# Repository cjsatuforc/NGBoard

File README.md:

# NGBoard
Next generation 3d printer controller board
## TODO
* Development
  * PCB Layout
  * BOM/Parts list
  * Switching regulator test
* Production
  * Software
  * Testing
* Profit

## Features
* 32 bit microcontroller (STM32F401VET)
* Trinamic tmc2130 drivers
* Raspberry pi/orange pi connector
* 12V or 24V 
* Direct connect inductive sensor

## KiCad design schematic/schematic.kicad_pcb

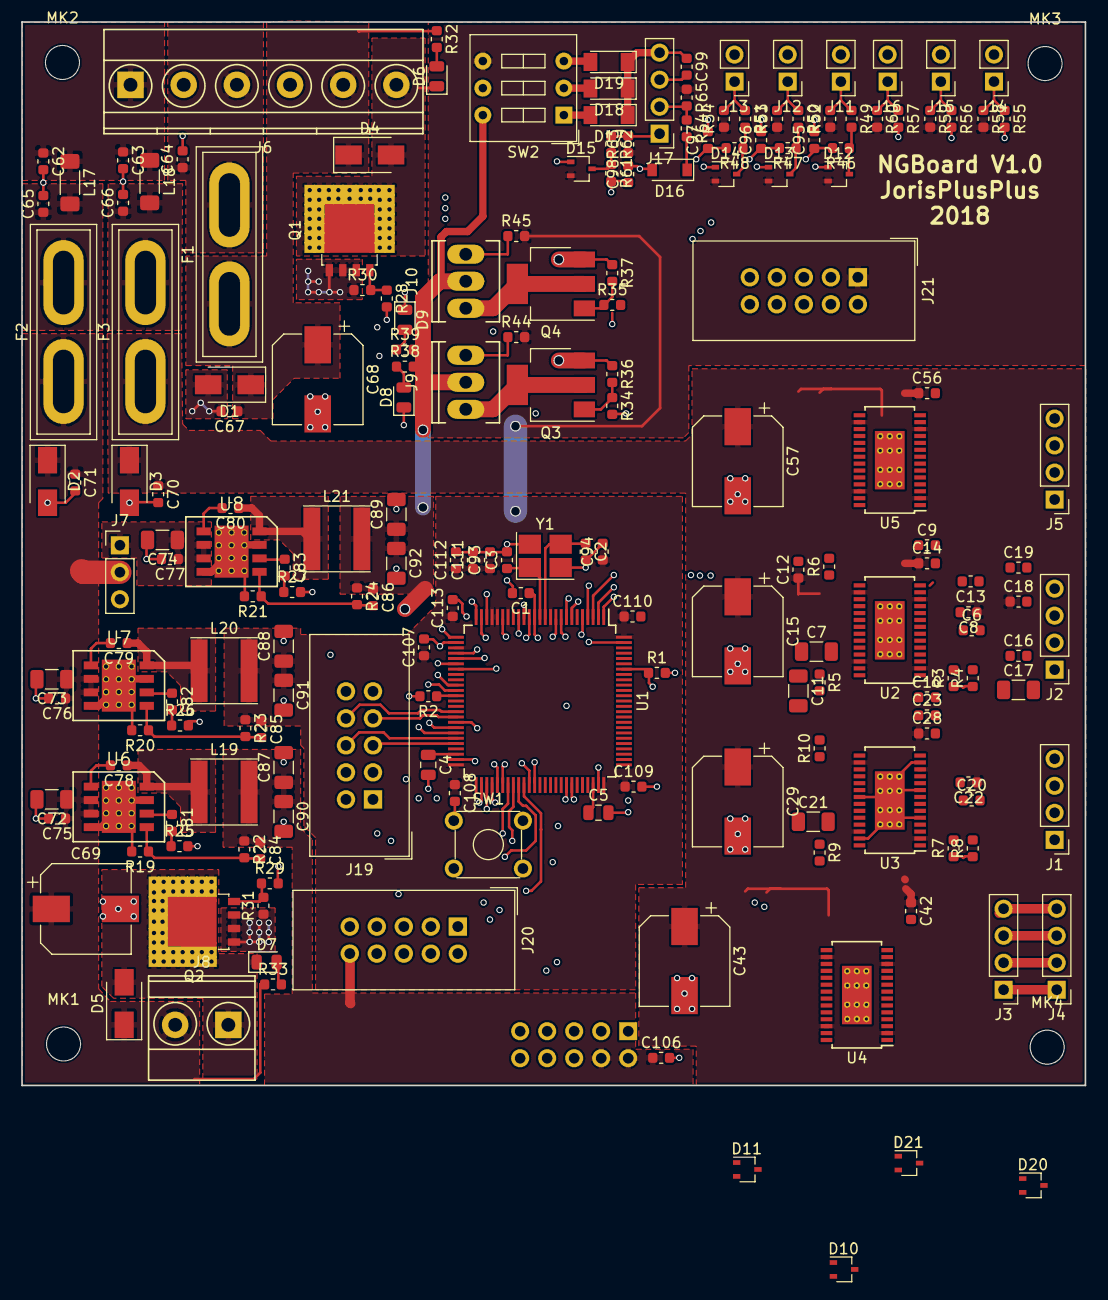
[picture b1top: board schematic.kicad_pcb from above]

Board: 4 copper layers, 100.0 x 100.0 mm, 197 parts (1 on the bottom side), 140 nets.

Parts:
C1, C6, C10, C16, C20, C62, C63, C64, C65, C66, C67, C70, C71, C75, C76, C77, C78, C79, C80, C94, C95, C96, C97, C98, C99, C106, C107, C108, C109, C110, C111, C112: 100nF; C_0603_1608Metric
C2, C3, C84: 18pF; C_0603_1608Metric
C4, C5: 2.2uF; C_0805_2012Metric
C7, C11, C17, C21, C87, C88, C89, C90, C91, C92: 22uF; C_1206_3216Metric
C8, C12, C14, C18, C22, C28, C42, C56: 220nF; C_0603_1608Metric
C9, C13, C19, C23: 10nF; C_0603_1608Metric
C15, C29, C43, C57, C68, C69: 100uF; CP_Elec_8x10
C72, C73, C74: 10uF; C_1206_3216Metric
C81, C82, C83: 6800pF; C_0603_1608Metric
C85, C86: 100pF; C_0603_1608Metric
C93: 4.7uF; C_0603_1608Metric
C113: 1uF; C_0603_1608Metric
D1, D2, D3: SMAJ24A; D_SMA
D4, D5: SK310A; D_SMA
D6, D7, D8, D9: LED; LED_0805_2012Metric
D10, D11, D12, D13, D14, D15, D20, D21: BAV99,215; SOT-323_SC-70
D16: 3.3V; D_SOD-123
D17, D18, D19: D; D_MiniMELF
F1: 15A; BladeFuse-CarType
F2, F3: 5A; BladeFuse-CarType
J1, J2, J3, J4, J5, J17: Conn_01x04; PinHeader_1x04_P2.54mm_Vertical
J6: Conn_01x06; TerminalBlock_Phoenix_MKDS1.5-6pol
J7: Conn_01x03; Socket_Strip_Straight_1x03_Pitch2.54mm
J8: Screw_Terminal_01x02; TerminalBlock_Phoenix_MKDS1.5-2pol
J9, J10: Conn_01x03; Socket_MOLEX-KK-RM2-54mm_Lock_3pin_straight
J11, J12, J13, J14, J15, J16: Conn_01x02; PinHeader_1x02_P2.54mm_Vertical
J18: Conn_02x05_Odd_Even; PinSocket_2x05_P2.54mm_Vertical
J19, J20, J21: Conn_02x05_Odd_Even; IDC-Header_2x05_P2.54mm_Vertical
L17, L18: 60R; L_1806_4516Metric
L19: 4.7uH; L_Taiyo-Yuden_NR-60xx
L20, L21: 3.3uH; L_Taiyo-Yuden_NR-60xx
MK1, MK2, MK3, MK4: Mounting_Hole; MountingHole_3.2mm_M3
Q1, Q2: PSMN1R7-30YL; SOT-669_LFPAK_ThermalVias-1
Q3, Q4: NCV8402; SOT-223
R1, R2, R25, R26, R27, R58, R59, R60, R65: 10K; R_0603_1608Metric
R3, R4, R5, R6, R7, R8, R9, R10: 39K; R_0603_1608Metric
R19: 19.1K; R_0603_1608Metric
R20: 32K; R_0603_1608Metric
R21: 7.15K; R_0603_1608Metric
R22, R23, R24, R30, R31, R36, R37: 100K; R_0603_1608Metric
R28, R29, R34, R35, R55, R56, R57, R64: 100; R_0603_1608Metric
R32, R33, R38, R39, R44, R45: 1.8K; R_0603_1608Metric
R46, R47, R48, R49, R50, R51, R61, R62: 2K37; R_0603_1608Metric
R52, R53, R54, R63: 4.7K; R_0603_1608Metric
SW1: SW_Push_Dual; SW_TH_Tactile_Omron_B3F-10xx
SW2: SW_DIP_x03; SW_DIP_x3_W7.62mm_Slide
U1: STM32F401VETx; LQFP-100_14x14mm_P0.5mm
U2, U3, U4, U5: L6470; HTSSOP-28-L6470
U6, U7, U8: BD9E302EFJ; SOIC-8
Y1: Crystal_GND24; Crystal_SMD_SeikoEpson_FA238-4Pin_3.2x2.5mm_HandSoldering

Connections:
+3V3: C6.1, C7.1, C10.1, C11.1, C16.1, C17.1, C20.1, C21.1, C85.1, C88.1, C91.1, C93.1, C94.1, C107.1, C108.1, C109.1, C110.1, C111.1, C112.1, C113.1, D12.2, D13.2, D14.2, D15.2, J21.1, L20.2, R3.1, R4.1, R5.1, R6.1, R7.1, R8.1, R9.1, R10.1, R23.1, R44.2, R45.2, R52.1, R53.1, R54.1, R58.2, R59.2, R60.2, R63.1, R65.1, SW2.4, U1.11, U1.19, U1.21, U1.22, U1.28, U1.50, U1.75, U1.100, U2.4, U2.6, U2.17, U3.4, U3.6, U3.17, U4.4, U4.6, U4.17, U5.4, U5.6, U5.17
+5V: C84.1, C87.1, C90.1, C106.1, J18.2, J18.4, J20.10, L19.2, R22.1, SW2.5
+12C: C8.1, C12.1, C14.1, C15.1, C18.1, C22.1, C28.1, C29.1, C42.1, C43.1, C56.1, C57.1, C70.1, D3.1, D10.1, D11.1, D20.1, D21.1, F3.1, U2.2, U2.12, U2.16, U2.26, U3.2, U3.12, U3.16, U3.26, U4.2, U4.12, U4.16, U4.26, U5.2, U5.12, U5.16, U5.26
+12V: C86.1, C89.1, C92.1, J7.3, J9.2, J10.2, L21.2, R24.1, R38.2, R39.2, SW2.6
+24V: C67.1, C68.1, D1.1, D4.1, F1.1, J6.5, R32.1
/Mosfets/BED: D4.2, D6.1, J6.6, Q1.5
/MotorE/A1: J5.2, U5.1
/MotorE/A2: J5.3, U5.28
/MotorE/B1: J5.1, U5.14
/MotorE/B2: J5.4, U5.15
/MotorE/BUSY: R10.2, U5.22
/MotorE/FLAG: R9.2, U5.24
/MotorX/A1: J2.2, U2.1
/MotorX/A2: J2.3, U2.28
/MotorX/B1: J2.1, U2.14
/MotorX/B2: J2.4, U2.15
/MotorX/BUSY: R4.2, U2.22
/MotorX/FLAG: R3.2, U2.24
/MotorY/A1: J1.2, U3.1
/MotorY/A2: J1.3, U3.28
/MotorY/B1: J1.1, U3.14
/MotorY/B2: J1.4, U3.15
/MotorY/BUSY: R6.2, U3.22
/MotorY/FLAG: R5.2, U3.24
/MotorZ/A1: J3.2, J4.2, U4.1
/MotorZ/A2: J3.3, J4.3, U4.28
/MotorZ/B1: J3.1, J4.1, U4.14
/MotorZ/B2: J3.4, J4.4, U4.15
/MotorZ/BUSY: R8.2, U4.22
/MotorZ/FLAG: R7.2, U4.24
BEEP: J20.1, U1.61
BOOT0: J18.3, R1.1, U1.94
BPWM: R28.2, U1.26
ENC1: J20.2, U1.62
ENC3: J19.5, U1.46
EPWM: R29.2, U1.24
F0PWM: R34.2, U1.23
F1PWM: R35.2, U1.25
GND: C1.2, C2.2, C3.2, C4.2, C5.2, C6.2, C7.2, C10.2, C11.2, C14.2, C15.2, C16.2, C17.2, C20.2, C21.2, C28.2, C29.2, C42.2, C43.2, C56.2, C57.2, C62.2, C63.2, C64.2, C65.2, C66.2, C67.2, C68.2, C69.2, C70.2, C71.2, C72.2, C73.2, C74.2, C75.2, C76.2, C77.2, C87.2, C88.2, C89.2, C90.2, C91.2, C92.2, C93.2, C94.2, C95.2, C96.2, C97.2, C98.2, C99.2, C106.2, C107.2, C108.2, C109.2, C110.2, C111.2, C112.2, C113.2, D1.2, D2.2, D3.2, D12.1, D13.1, D14.1, D15.1, D16.2, J6.2, J6.4, J11.2, J12.2, J13.2, J14.2, J15.2, J16.2, J17.3, J18.6, J18.9, J20.9, J21.2, Q1.1, Q1.2, Q1.3, Q2.1, Q2.2, Q2.3, Q3.3, Q4.3, R1.2, R2.2, R19.2, R20.2, R21.2, R25.2, R26.2, R27.2, R30.1, R31.1, R36.1, R37.1, SW1.1, SW1.3, U1.10, U1.20, U1.27, U1.49, U1.74, U1.99, U2.5, U2.9, U2.13, U2.21, U2.27, U2.29, U3.5, U3.9, U3.13, U3.21, U3.27, U3.29, U4.5, U4.9, U4.13, U4.21, U4.27, U4.29, U5.5, U5.9, U5.13, U5.21, U5.27, U5.29, U6.4, U6.7, U6.9, U7.4, U7.7, U7.9, U8.4, U8.7, U8.9, Y1.2, Y1.4
GP1: J21.3, U1.4
GP2: J21.4, U1.5
GP3: J21.5, U1.7
GP4: J21.6, U1.8
GP5: J21.7, U1.9
GP6: J21.8, U1.15
GP7: J21.9, U1.16
GP8: J21.10, U1.17
LCD4: J20.5, U1.55
LCD5: J20.6, U1.56
LCD6: J20.7, U1.57
LCD7: J20.8, U1.58
LCDE: J20.3, U1.60
LCDRS: J20.4, U1.59
MISO: U1.53, U2.18, U3.18, U4.18, U5.18
MOSI: U1.54, U2.20, U3.20, U4.20, U5.20
unnamed: C2.1, U1.12, Y1.3
unnamed: C3.1, U1.13, Y1.1
unnamed: C4.1, U1.48
unnamed: C5.1, U1.73
unnamed: C8.2, D10.2, U2.11
unnamed: C9.1, D10.3
unnamed: C9.2, U2.10
unnamed: C12.2, D11.2, U3.11
unnamed: C13.1, D11.3
unnamed: C13.2, U3.10
unnamed: C18.2, D20.2, U4.11
unnamed: C19.1, D20.3
unnamed: C19.2, U4.10
unnamed: C22.2, D21.2, U5.11
unnamed: C23.1, D21.3
unnamed: C23.2, U5.10
unnamed: C62.1, C63.1, J6.1, L17.1, L18.1
unnamed: C64.1, F1.2, J6.3
unnamed: C65.1, F2.2, L17.2
unnamed: C66.1, F3.2, L18.2
unnamed: C74.1, C77.1, J7.1, U8.2, U8.3
unnamed: C78.1, L19.1, U6.8
unnamed: C78.2, U6.1
unnamed: C79.1, L20.1, U7.8
unnamed: C79.2, U7.1
unnamed: C80.1, L21.1, U8.8
unnamed: C80.2, U8.1
unnamed: C81.1, U6.6
unnamed: C81.2, R25.1
unnamed: C82.1, U7.6
unnamed: C82.2, R26.1
unnamed: C83.1, U8.6
unnamed: C83.2, R27.1
unnamed: C84.2, R19.1, R22.2, U6.5
unnamed: C85.2, R20.1, R23.2, U7.5
unnamed: C86.2, R21.1, R24.2, U8.5
unnamed: C99.1, D17.1, D18.1, D19.1, J17.4
unnamed: D5.2, D7.1, J8.1, Q2.5
unnamed: D6.2, R32.2
unnamed: D7.2, R33.2
unnamed: D8.1, J9.1, Q3.2, Q3.4
unnamed: D8.2, R38.1
unnamed: D9.1, J10.1, Q4.2, Q4.4
unnamed: D9.2, R39.1
unnamed: D12.3, R46.1, R49.2
unnamed: D13.3, R47.1, R50.2
unnamed: D14.3, R48.1, R51.2
unnamed: D15.3, R61.1, R62.2
unnamed: D17.2, SW2.1
unnamed: D18.2, SW2.2
unnamed: D19.2, SW2.3
unnamed: J11.1, R49.1, R52.2
unnamed: J12.1, R50.1, R53.2
unnamed: J13.1, R51.1, R54.2
unnamed: J14.1, R55.1, R58.1
unnamed: J15.1, R56.1, R59.1
unnamed: J16.1, R57.1, R60.1
unnamed: J17.1, R62.1, R63.2
unnamed: J17.2, R64.1, R65.2
unnamed: Q1.4, R28.1, R30.2
unnamed: Q2.4, R29.1, R31.2
unnamed: Q3.1, R34.1, R36.2
unnamed: Q4.1, R35.1, R37.2
unnamed: R2.1, U1.37
RESET: J19.8, U1.40
RST: C1.1, J18.5, SW1.2, SW1.4, U1.14
RX: J18.8, U1.69
SCK: U1.52, U2.19, U3.19, U4.19, U5.19
SDCLK: J19.2, U1.43
SDDETECT: J19.7, U1.41
SDMISO: J19.1, U1.44
SDMOSI: J19.6, U1.45
SDSS: J19.4, U1.42
T0: J9.3, R44.1, U1.35
T1: J10.3, R45.1, U1.36
THERM0: C95.1, R46.2, U1.29
THERM1: C96.1, R47.2, U1.30
THERM2: C97.1, R48.2, U1.31
THERM3: C98.1, R61.2, U1.32
TX: J18.10, U1.68
VBUS: C69.1, C71.1, C72.1, C73.1, C75.1, C76.1, D2.1, D5.1, F2.1, J7.2, J8.2, R33.1, U6.2, U6.3, U7.2, U7.3
XEND: R55.2, U1.3
YEND: R56.2, U1.2
ZEND: R57.2, U1.1
ZPROBE: D16.1, R64.2

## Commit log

2018-01-29 Removed backups
2018-01-29 Power layout single driver done
2018-01-29 Most power routed to drivers
2018-01-30 Moved capacitors for better power connection
2018-01-30 More driver routing
2018-01-30 main power plains routed
2018-01-30 Started initial spi routing
2018-01-30 routed 3.3V power and start re arange signals
2018-01-30 Reassigned signals to driver for easier routing
2018-01-30 Routed signals to E driver
2018-01-30 Routed all control signals to drivers
2018-01-30 More routing done
2018-01-31 Added display headers
2018-01-31 3.3V to upper area of the board
2018-01-31 Routed current pwm drivers
2018-01-31 Routed signals to pi connector
2018-01-31 Saved layout
2018-02-01 Routed thermal sensors
2018-02-03 Finished routing
2018-02-03 Added GPIO header
2018-02-03 Route gpio header
2018-02-04 Fixed C93 footprint
2018-02-04 Changed footprint size of some capacitors
2018-02-04 updated footprint bat54sw
2018-02-04 Updated inductor footprint
2018-02-04 Fixed inductor footprint
2018-02-04 Switch orange pi to raspberry pi zero w because the price difference is small
2018-04-09 Added bom
2018-04-16 Update regulators
2018-04-19 Updated to kicad 5.0.0
2018-04-22 Revert "Updated to kicad 5.0.0"
    This reverts commit 6c14fa6c8e6361c9b9ee4065803a5a63755fc6a7.
2018-04-23 Removed some components
2018-04-23 Added logo's and stm32 capacitors
2018-04-23 Added ground pours to internal layers
2018-04-23 Saved schematic
2018-08-16 Updated to kicad v5
2018-08-16 Moved to L6470 driver
2018-08-16 L6470 kicad library
